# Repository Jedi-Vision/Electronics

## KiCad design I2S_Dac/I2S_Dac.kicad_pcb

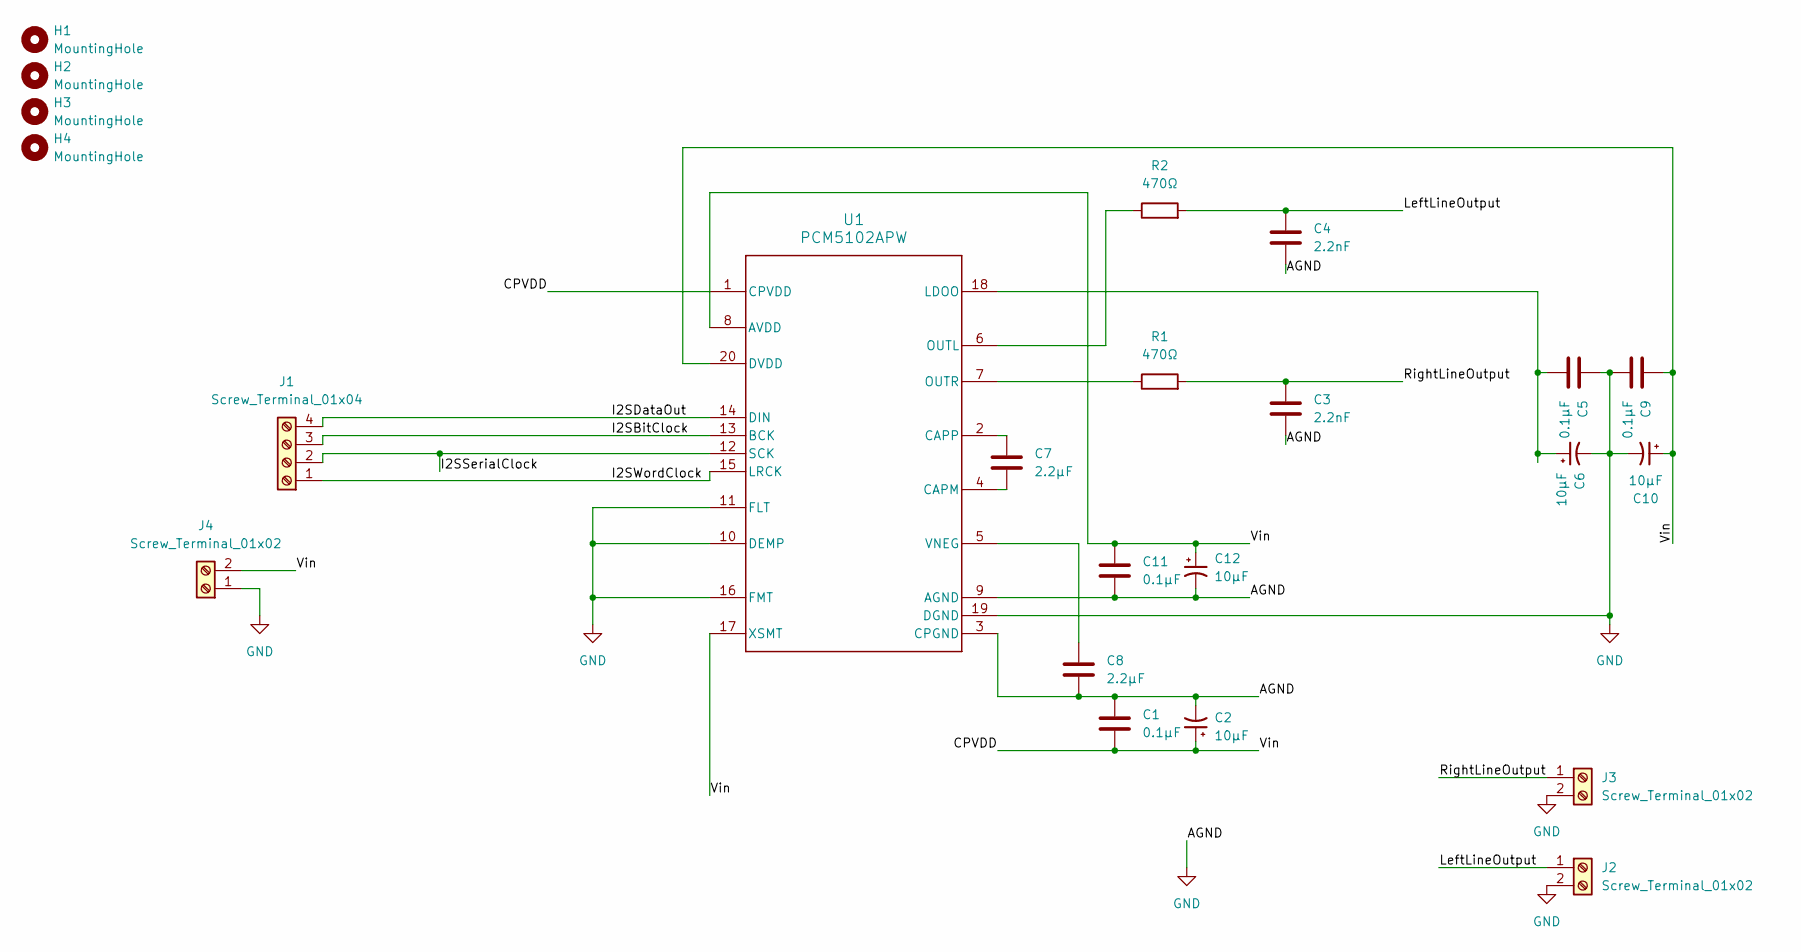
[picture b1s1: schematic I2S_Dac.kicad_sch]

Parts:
C1, C5, C9, C11: 0.1µF; C_1206_3216Metric
C2, C6, C10, C12: 10µF; C_1206_3216Metric
C3, C4: 2.2nF; C_1206_3216Metric
C7, C8: 2.2µF; C_1206_3216Metric
H1, H2, H3, H4: MountingHole; MountingHole_2.2mm_M2
J1: Screw_Terminal_01x04; TerminalBlock_Phoenix_MKDS-1,5-5_1x05_P5.00mm_Horizontal
J2, J3, J4: Screw_Terminal_01x02; TerminalBlock_Phoenix_MKDS-1,5-2_1x02_P5.00mm_Horizontal
R1, R2: 470Ω; R_1206_3216Metric
U1: PCM5102APW; PW0020A_N

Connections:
/CPVDD: C1.2, C2.1, C9.1, C10.1, C11.1, C12.1, J4.2, U1.1 (CPVDD), U1.8 (AVDD), U1.17 (XSMT), U1.20 (DVDD)
/I2SBitClock: J1.3, U1.13 (BCK)
/I2SDataOut: J1.4, U1.14 (DIN)
/I2SSerialClock: J1.2, U1.12 (SCK)
/I2SWordClock: J1.1, U1.15 (LRCK)
/LeftLineOutput: C4.1, J2.1, R2.2
/RightLineOutput: C3.1, J3.1, R1.2
GND: C1.1, C2.2, C3.2, C4.2, C5.1, C6.2, C8.1, C9.2, C10.2, C11.2, C12.2, J2.2, J3.2, J4.1, U1.3 (CPGND), U1.9 (AGND), U1.10 (DEMP), U1.11 (FLT), U1.16 (FMT), U1.19 (DGND)
unnamed: C7.2, U1.4 (CAPM)
unnamed: C7.1, U1.2 (CAPP)
unnamed: C5.2, C6.1, U1.18 (LDOO)
unnamed: R2.1, U1.6 (OUTL)
unnamed: R1.1, U1.7 (OUTR)
unnamed: C8.2, U1.5 (VNEG)

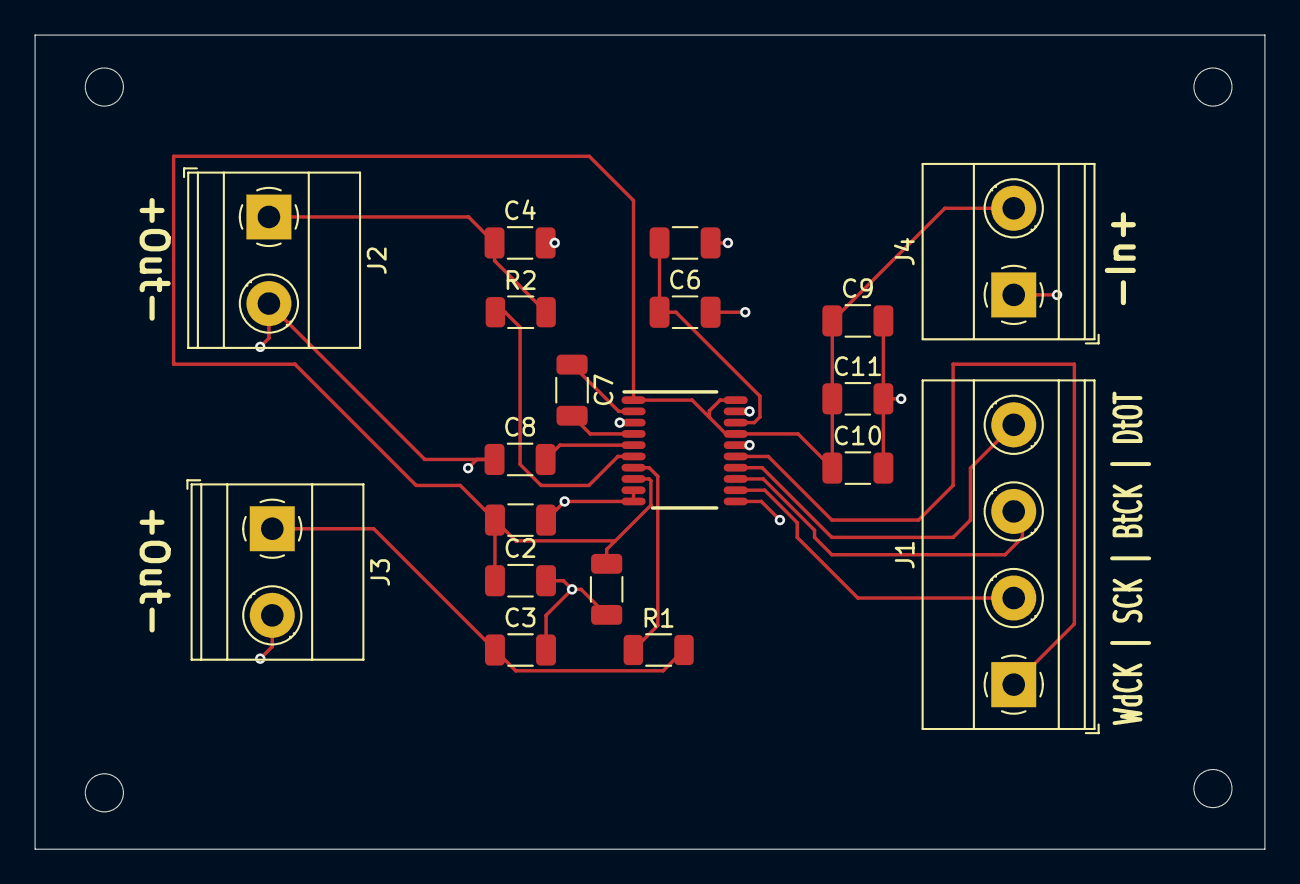
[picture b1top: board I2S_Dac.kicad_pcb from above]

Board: 2 copper layers, 71.0 x 47.0 mm, 23 parts (0 on the bottom side), 14 nets.

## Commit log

2025-11-16 Final I2S DAC Block KiCad
